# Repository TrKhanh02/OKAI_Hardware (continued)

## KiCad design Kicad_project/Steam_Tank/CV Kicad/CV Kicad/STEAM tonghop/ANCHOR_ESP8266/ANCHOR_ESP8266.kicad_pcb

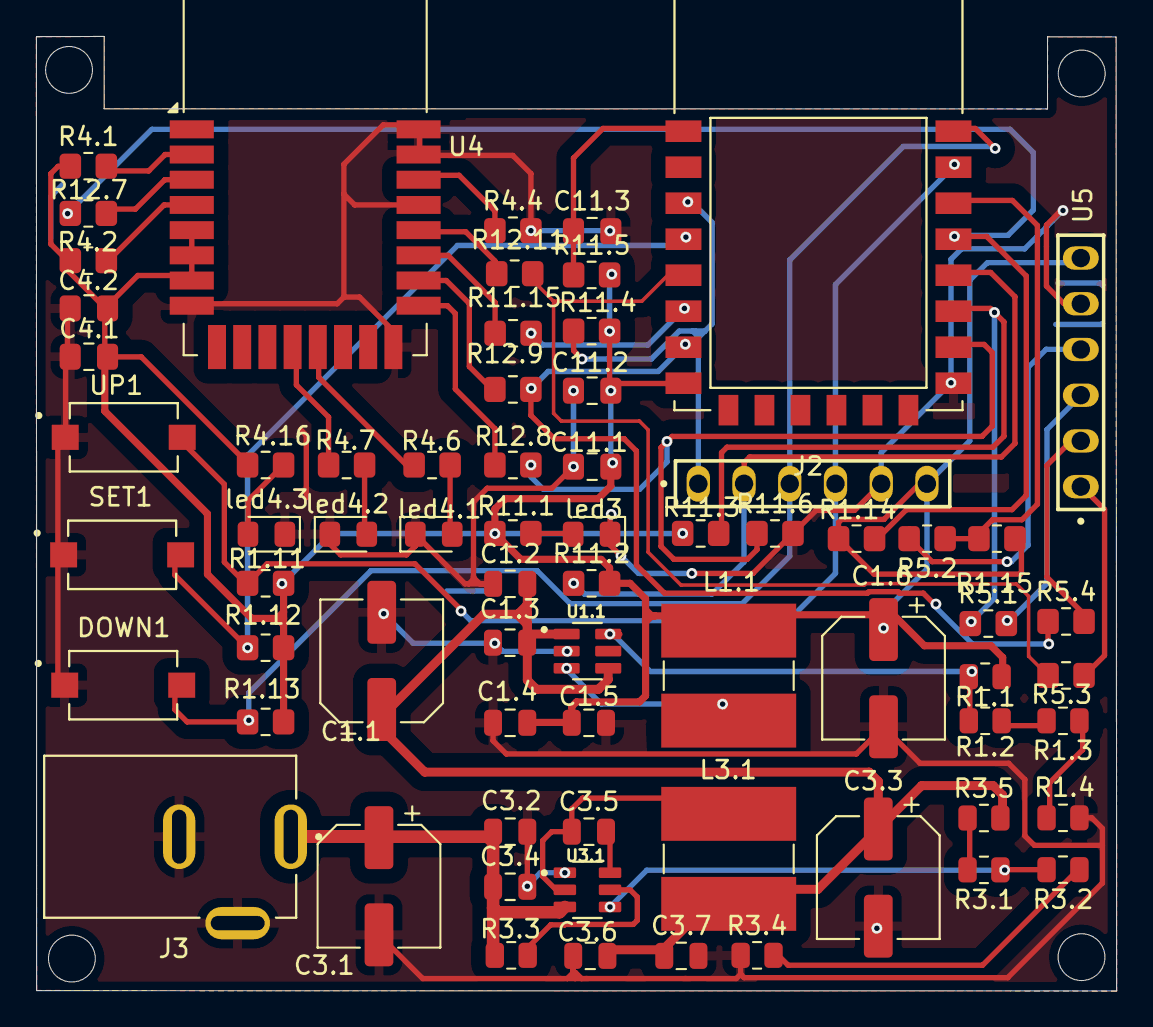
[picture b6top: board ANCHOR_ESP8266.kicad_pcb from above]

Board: 2 copper layers, 60.0 x 53.0 mm, 69 parts (0 on the bottom side), 45 nets.

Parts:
C1.1, C1.6, C3.1, C3.3: 220uF; CP_Elec_6.3x7.7
C1.2, C1.5, C3.2, C3.7: 10uF; C_0805_2012Metric
C1.3, C1.4, C3.4, C3.5, C3.6: 0.1uF; C_0805_2012Metric
C4.1, C11.1: 106; C_0805_2012Metric_Pad1.18x1.45mm_HandSolder
C4.2, C11.2, C11.3: 104; C_0805_2012Metric_Pad1.18x1.45mm_HandSolder
DOWN1: TS10-63-26-BE-250-SMT-TR; SW_TS10-63-26-BE-250-SMT-TR
J2: MTSW-106-08-L-S-295; SAMTEC_MTSW-106-08-L-S-295
J3: PJ-035D; CUI_PJ-035D
L1.1, L3.1: 22uH; L_Ferrocore_DLG-0705
R1.1, R3.1: 100K; R_0805_2012Metric
R1.2, R1.3, R3.2, R3.3, R3.4, R3.5: 10K; R_0805_2012Metric
R1.4: 3,3K; R_0805_2012Metric
R1.11, R1.12, R1.13, R1.14, R1.15, R4.4, R11.2, R11.3, R11.4, R11.5, R11.6: 10K; R_0805_2012Metric_Pad1.20x1.40mm_HandSolder
R4.1, R4.2: 10k; R_0805_2012Metric_Pad1.20x1.40mm_HandSolder
R4.6, R4.7, R4.16, R11.1: 470R; R_0805_2012Metric_Pad1.20x1.40mm_HandSolder
R5.1, R5.2, R5.3, R5.4, R11.15, R12.7, R12.8, R12.9, R12.11: 0R; R_0805_2012Metric_Pad1.20x1.40mm_HandSolder
SET1: TS10-63-26-BE-250-SMT-TR; SW_TS10-63-26-BE-250-SMT-TR
U1.1: TLV62569PDDCR; SOT95P280X110-6N
U3.1: TPS563201DDCR; SOT95P280X110-6N
U4: DWM1000
U5: LCD; SAMTEC_MTSW-106-08-L-S-295
U11: ESP8266-12E_ESP-12E; XCVR_ESP8266-12E_ESP-12E
UP1: TS10-63-26-BE-250-SMT-TR; SW_TS10-63-26-BE-250-SMT-TR
led3, led4.1, led4.2, led4.3: LED_Small_Filled; LED_0805_2012Metric_Pad1.15x1.40mm_HandSolder

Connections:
/5V: C1.1.1, C1.2.1, C1.3.1, C3.3.1, C3.6.1, C3.7.1, L3.1.2, R3.5.2, U1.1.1 (EN), U1.1.4 (VIN)
/12VDC: C3.1.1, C3.2.1, C3.4.1, J3.1, R3.3.2, U3.1.3 (VIN)
/8266_EN: J2.01, R11.4.1, U11.3 (EN)
/8266_IO0: J2.02, R11.2.1, U11.18 (IO0)
/8266_IO2: R5.1.1, R11.3.1, U11.17 (IO2)
/8266_IO4: R1.14.1, R12.7.1, U11.19 (IO4)
/8266_IO5: R1.15.1, R5.2.1, U11.20 (IO5)
/8266_IO12: R11.15.1, U11.6 (IO12)
/8266_IO13: R5.4.1, R12.9.1, U11.7 (IO13)
/8266_IO14: R5.3.1, R12.11.1, U11.5 (IO14)
/8266_IO15: R11.6.1, R12.8.1, U11.16 (IO15)
/8266_IO16: R1.12.2, SET1.2, U11.4 (IO16)
/8266_RST: C11.3.1, R11.5.1, U11.1 (RESET)
/8266_RX: J2.04, R1.11.2, U11.21 (RXD), UP1.2
/8266_TX: DOWN1.2, J2.03, R1.13.2, U11.22 (TXD)
/DWM_CLK: R12.11.2, U4.20 (SPICLK)
/DWM_CS: R12.8.2, U4.17 (~SPICS)
/DWM_IRQ: R4.4.1, U4.22 (IRQ/GPIO8)
/DWM_MISO: R11.15.2, U4.19 (SPIMISO)
/DWM_MOSI: R12.9.2, U4.18 (SPIMOSI)
/DWM_RST: R12.7.2, U4.3 (~RST)
/FB_U1.1: R1.1.1, R1.2.2, U1.1.6 (FB)
/LCD_CLK: R5.3.2, U5.01
/LCD_CS: R5.2.2, U5.04
/LCD_DC: R5.1.2, U5.03
/LCD_MOSI: R5.4.2, U5.02
/VDD33: C1.4.1, C1.5.1, C1.6.1, C4.1.1, C4.2.1, C11.1.1, C11.2.1, J2.06, L1.1.1, R1.1.2, R1.11.1, R1.12.1, R1.13.1, R1.14.2, R1.15.2, R4.1.1, R4.2.1, R4.16.2, R11.1.1, R11.2.2, R11.3.2, R11.4.2, R11.5.2, U4.5 (VDDAON), U4.6 (VDD3V3), U4.7 (VDD3V3), U5.06, U11.8 (VCC)
GND: C1.1.2, C1.2.2, C1.3.2, C1.4.2, C1.5.2, C1.6.2, C3.1.2, C3.2.2, C3.3.2, C3.4.2, C3.6.2, C3.7.2, C4.1.2, C4.2.2, C11.1.2, C11.2.2, C11.3.2, DOWN1.1, J2.05, J3.2, J3.3, R1.4.1, R3.4.1, R4.4.2, R11.6.2, SET1.1, U1.1.2 (GND), U3.1.1 (GND), U4.8 (VSS), U4.16 (VSS), U4.21 (VSS), U4.23 (VSS), U4.24 (VSS), U5.05, U11.15 (GND), UP1.1, led3.1 (K), led4.1.1 (K), led4.2.1 (K), led4.3.1 (K)
unnamed: R1.2.1, R1.3.2
unnamed: R1.3.1, R1.4.2
unnamed: R3.1.2, R3.5.1
unnamed: R3.2.1, R3.4.2
unnamed: L1.1.2, U1.1.3 (SW)
unnamed: R3.3.1, U3.1.5 (EN)
unnamed: C3.5.1, L3.1.1, U3.1.2 (SW)
unnamed: C3.5.2, U3.1.6 (VBST)
unnamed: R3.1.1, R3.2.2, U3.1.4 (VFB)
unnamed: R4.6.1, U4.13 (GPIO2/RXLED)
unnamed: R4.7.1, U4.12 (GPIO3/TXLED)
unnamed: R4.2.2, U4.4 (GPIO7)
unnamed: R4.1.2, U4.2 (WAKEUP)
unnamed: R11.1.2, led3.2 (A)
unnamed: R4.6.2, led4.1.2 (A)
unnamed: R4.7.2, led4.2.2 (A)
unnamed: R4.16.1, led4.3.2 (A)

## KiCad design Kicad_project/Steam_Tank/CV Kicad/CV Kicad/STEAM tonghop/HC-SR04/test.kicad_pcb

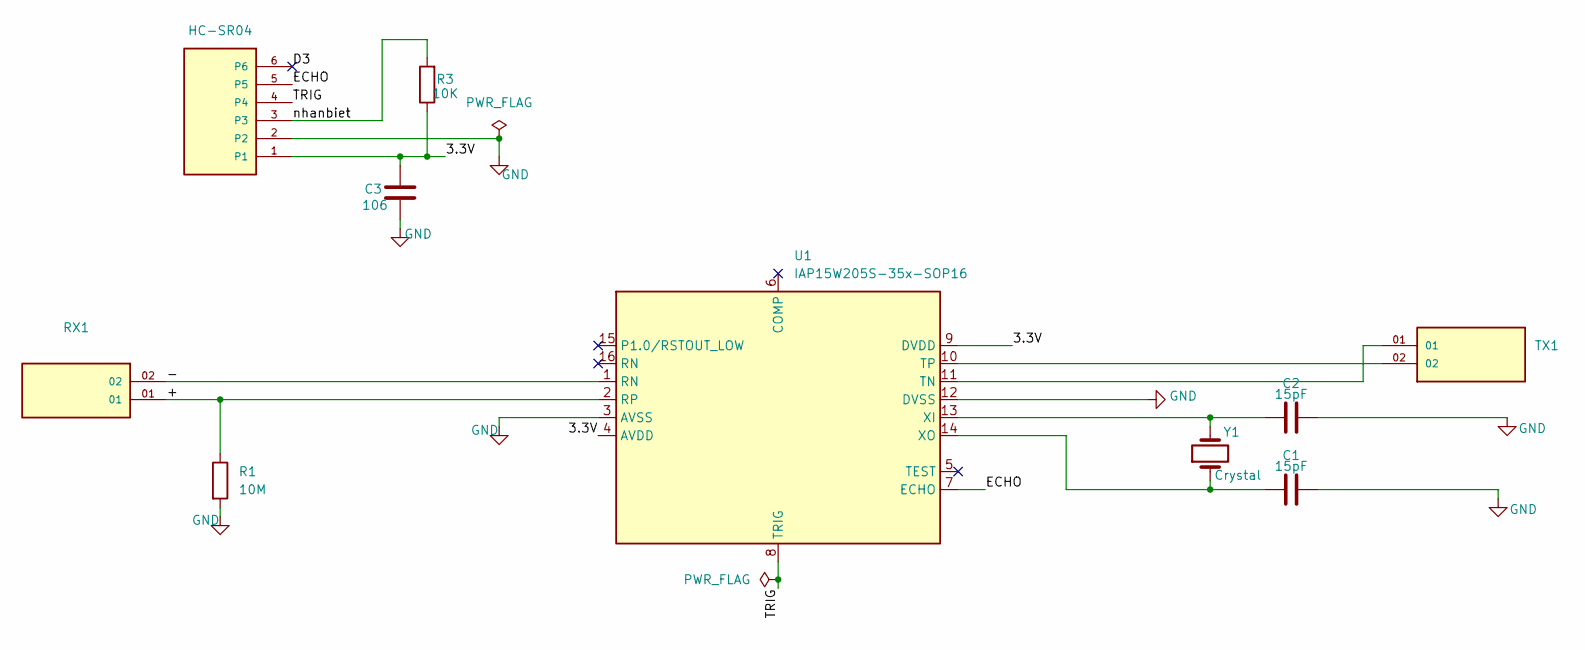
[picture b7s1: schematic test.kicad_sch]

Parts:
C1, C2: 15pF; C_0805_2012Metric_Pad1.18x1.45mm_HandSolder
C3: 106; C_0805_2012Metric_Pad1.18x1.45mm_HandSolder
R1: 10M; R_0805_2012Metric_Pad1.20x1.40mm_HandSolder
R3: 10K; R_0805_2012Metric_Pad1.20x1.40mm_HandSolder
RJ11: HC-SR04; TE_RJ11-6N-B; PART_DESCRIPTION CONN MOD JACK 6P6C R/A UNSHLD
RX1: TSW-102-23-T-S; SAMTEC_TSW-102-23-T-S; PARTREV R
TX1: TSW-102-23-T-S; SAMTEC_TSW-102-23-T-S; PARTREV R
U1: IAP15W205S-35x-SOP16; STC_SOP-16_3.9x9.9mm_P1.27mm
Y1: Crystal; Crystal_HC18-U_Vertical

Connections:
/3.3V: C3.2, R3.1, RJ11.1, U1.4 (AVDD), U1.9 (DVDD); also elsewhere on the board
/+: R1.1, RX1.01, U1.2 (RP)
/-: RX1.02, U1.1 (RN)
/D3: RJ11.6
/ECHO: RJ11.5, U1.7 (ECHO)
/TRIG: RJ11.4, U1.8 (TRIG)
/nhanbiet: R3.2, RJ11.3
GND: C1.2, C2.2, C3.1, R1.2, RJ11.2, U1.3 (AVSS), U1.12 (DVSS)
unnamed: TX1.01, U1.11 (TN)
unnamed: TX1.02, U1.10 (TP)
unnamed: C2.1, U1.13 (XI), Y1.2
unnamed: C1.1, U1.14 (XO), Y1.1

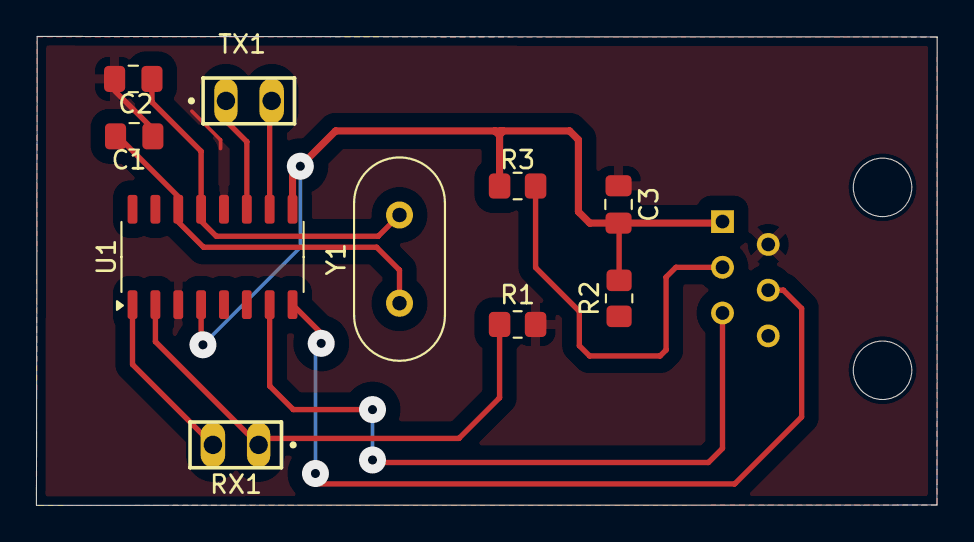
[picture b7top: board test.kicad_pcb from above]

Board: 2 copper layers, 50.0 x 26.1 mm, 11 parts (1 on the bottom side), 11 nets.

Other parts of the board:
R2: R; R_0805_2012Metric_Pad1.20x1.40mm_HandSolder

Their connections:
/3.3V: R2.2; also elsewhere on the board
